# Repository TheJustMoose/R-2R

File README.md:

# R-2R
Hard&amp;Soft for Arduino R-2R 8 bit DAC

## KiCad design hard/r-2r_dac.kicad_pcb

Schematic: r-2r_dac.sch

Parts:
C1: 0,33uF; C_Disc_D4.7mm_W2.5mm_P5.00mm
C2: 0,1uF; C_Disc_D4.7mm_W2.5mm_P5.00mm
C3: 20uF; CP_Radial_D5.0mm_P2.50mm
C4: 220uF; CP_Radial_D6.3mm_P2.50mm
D1, D2: 1N4148; D_DO-35_SOD27_P7.62mm_Horizontal
J1: Conn_01x04_Male; PinHeader_1x04_P2.54mm_Vertical
J2: Conn_01x08_Male; PinHeader_1x08_P2.54mm_Vertical
J3, J4, J5, J7, J8, J9: Conn_01x01_Male; PinHeader_1x01_P2.54mm_Vertical
J6: Conn_01x02_Male; PinHeader_1x02_P2.54mm_Vertical
MH1, MH2, MH3, MH4: MountingHole; MountingHole_3.2mm_M3
Q1: BD135; TO-126-3_Vertical
Q2: BD136; TO-126-3_Vertical
R1, R3, R5: 4,7k; R_Axial_DIN0207_L6.3mm_D2.5mm_P10.16mm_Horizontal
R2, R4, R6, R7: 10k; R_Axial_DIN0207_L6.3mm_D2.5mm_P10.16mm_Horizontal
R8, R9, R10, R11, R12, R13, R14, R15, R16: 2k; R_Axial_DIN0207_L6.3mm_D2.5mm_P10.16mm_Horizontal
R17, R18, R19, R20, R21, R22, R23, R26, R27: 1k; R_Axial_DIN0207_L6.3mm_D2.5mm_P10.16mm_Horizontal
R24, R25: R; R_Axial_DIN0207_L6.3mm_D2.5mm_P10.16mm_Horizontal
RV1: 20k; Potentiometer_Piher_PT-10-V10_Vertical
U1: L78L33_TO92; TO-92_Inline
U2: 74HC595; DIP-16_W7.62mm_Socket
U3: LM358; DIP-8_W7.62mm_Socket

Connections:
GND: C1.2, C2.2, J1.4, J3.1, J5.1, J6.1, J7.1, J9.1, Q2.2 (C), R2.2, R4.2, R6.2, R16.1, R25.2, R27.2, RV1.3, U1.2 (GND), U2.8, U2.13, U3.4 (V-)
unnamed: C2.1, R7.1, U1.1 (VO), U2.16
unnamed: C3.1, R24.2, R25.1, U3.5 (+)
unnamed: C3.2, RV1.2
unnamed: C4.1, Q1.1 (E), Q2.1 (E), U3.6 (-)
unnamed: C4.2, J6.2
unnamed: D1.1, D2.2, U3.7
unnamed: D1.2, Q1.3 (B), R26.2
unnamed: D2.1, Q2.3 (B), R27.1
unnamed: J1.1, R5.1
unnamed: J1.2, R3.1
unnamed: J1.3, R1.1
unnamed: J2.1, R8.2, U2.15
unnamed: J2.2, R9.2, U2.1
unnamed: J2.3, R10.2, U2.2
unnamed: J2.4, R11.2, U2.3
unnamed: J2.5, R12.2, U2.4
unnamed: J2.6, R13.2, U2.5
unnamed: J2.7, R14.2, U2.6
unnamed: J2.8, R15.2, U2.7
unnamed: R1.2, R2.1, U2.14
unnamed: R3.2, R4.1, U2.11
unnamed: R5.2, R6.1, U2.12
unnamed: R7.2, U2.10
unnamed: R10.1, R18.2, R19.1
unnamed: R11.1, R19.2, R20.1
unnamed: R12.1, R20.2, R21.1
unnamed: R13.1, R21.2, R22.1
unnamed: R14.1, R22.2, R23.1
unnamed: R15.1, R23.2, U3.3 (+)
unnamed: R8.1, R16.2, R17.1
unnamed: R9.1, R17.2, R18.1
unnamed: RV1.1, U3.1, U3.2 (-)
VCC: C1.1, J4.1, J8.1, Q1.2 (C), R24.1, R26.1, U1.3 (VI), U3.8 (V+)

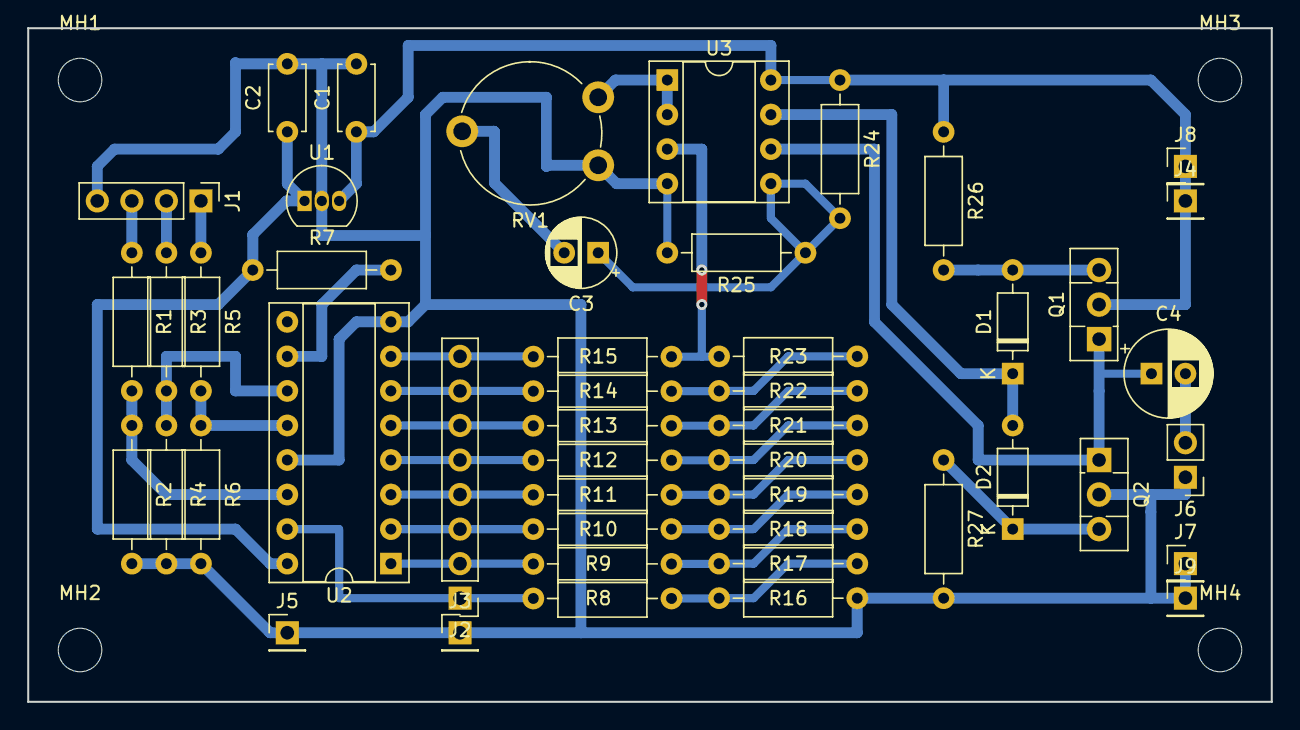
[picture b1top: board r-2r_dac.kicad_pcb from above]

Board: 2 copper layers, 91.4 x 49.5 mm, 52 parts (0 on the bottom side), 34 nets.

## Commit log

2018-08-24 Just picture
2018-08-27 in work
2018-08-28 Last tracks
2018-08-28 Just data for DAC
2018-08-28 New render
2018-08-30 Some code to play audio
2018-08-30 This script print to screen sin(i) where i == 0 - 2*PI
2018-08-30 Just add comma
2018-08-31 Fix build
2018-08-31 Try to unify code
